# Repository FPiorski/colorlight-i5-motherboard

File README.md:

# colorlight-i5-motherboard
A base board for the colorlight i5 FPGA module with a bunch of connectors

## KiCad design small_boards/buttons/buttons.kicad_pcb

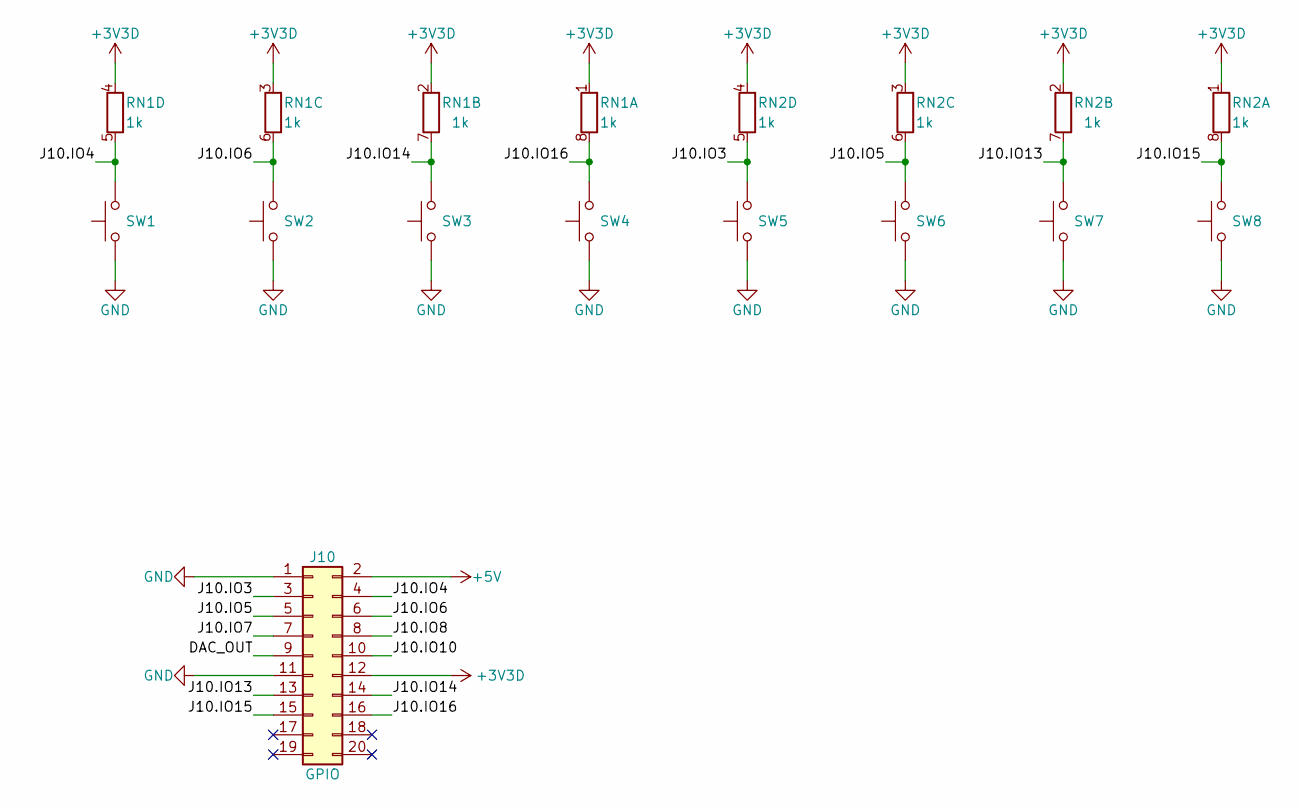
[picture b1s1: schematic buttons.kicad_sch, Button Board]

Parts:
J10: GPIO; PinSocket_2x10_P2.54mm_Vertical; LCSC C2897411
RN1, RN2: 1k; R_Array_Convex_4x0603; LCSC C160614
SW1, SW2, SW3, SW4, SW5, SW6, SW7, SW8: SW_Push_1P1T_NO_6x6mm_H9.5mm; LCSC C294566

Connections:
+3V3D: J10.12, RN1.1 (R1.1), RN1.2 (R2.1), RN1.3 (R3.1), RN1.4 (R4.1), RN2.1 (R1.1), RN2.2 (R2.1), RN2.3 (R3.1), RN2.4 (R4.1)
+5V: J10.2
/DAC_OUT: J10.9
/J10.IO3: J10.3, RN2.5 (R4.2), SW5.2
/J10.IO4: J10.4, RN1.5 (R4.2), SW1.2
/J10.IO5: J10.5, RN2.6 (R3.2), SW6.2
/J10.IO6: J10.6, RN1.6 (R3.2), SW2.2
/J10.IO7: J10.7
/J10.IO8: J10.8
/J10.IO10: J10.10
/J10.IO13: J10.13, RN2.7 (R2.2), SW7.2
/J10.IO14: J10.14, RN1.7 (R2.2), SW3.2
/J10.IO15: J10.15, RN2.8 (R1.2), SW8.2
/J10.IO16: J10.16, RN1.8 (R1.2), SW4.2
GND: J10.1, J10.11, SW1.1, SW2.1, SW3.1, SW4.1, SW5.1, SW6.1, SW7.1, SW8.1

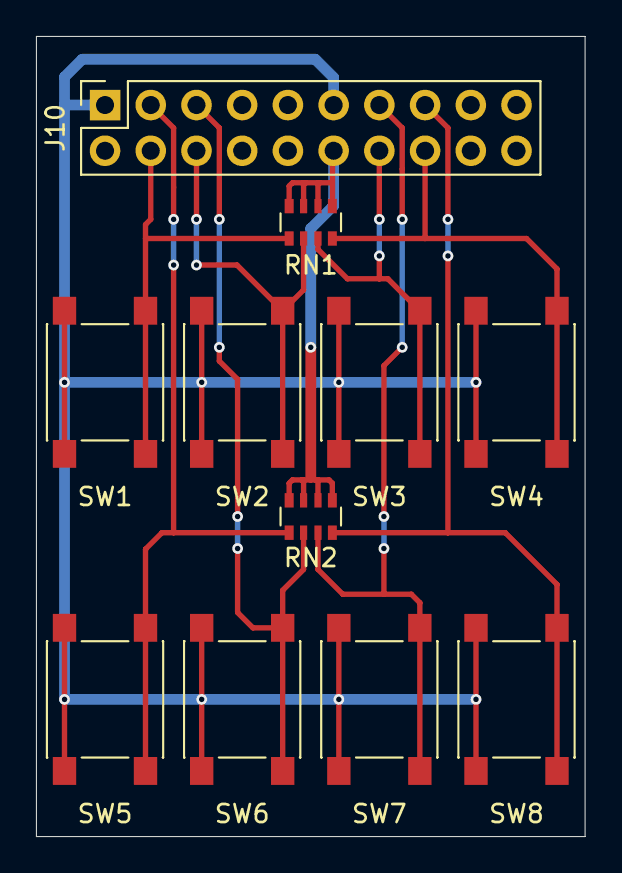
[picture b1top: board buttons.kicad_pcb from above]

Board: 2 copper layers, 30.5 x 44.5 mm, 11 parts (0 on the bottom side), 10 nets.

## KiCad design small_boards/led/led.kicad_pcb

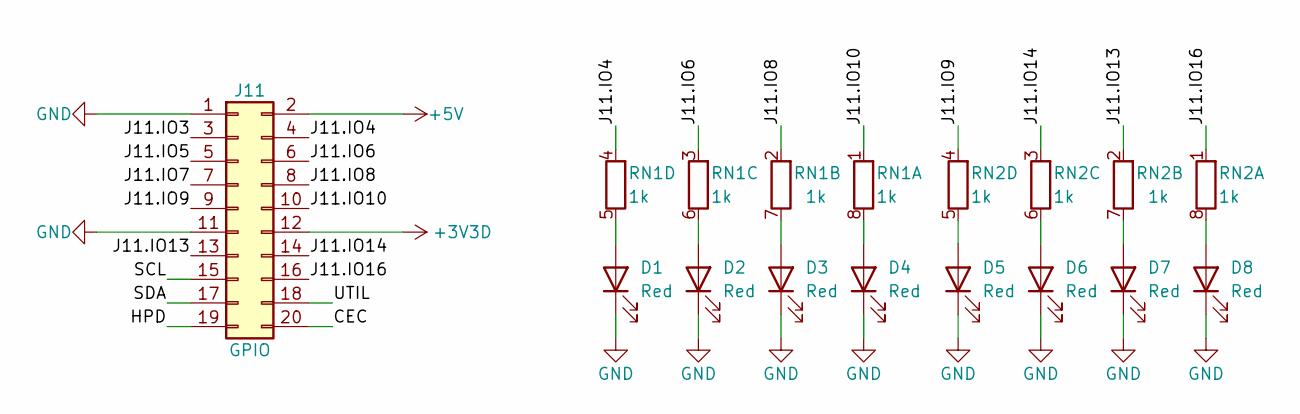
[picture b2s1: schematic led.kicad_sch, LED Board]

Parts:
D1, D2, D3, D4, D5, D6, D7, D8: Red; LED_0805_2012Metric_Pad1.15x1.40mm_HandSolder; LCSC C84256
J11: GPIO; PinSocket_2x10_P2.54mm_Vertical; LCSC C2897411
RN1, RN2: 1k; R_Array_Convex_4x0603; LCSC C160614

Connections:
+3V3D: J11.12
+5V: J11.2
/CEC: J11.20
/HPD: J11.19
/J11.IO3: J11.3
/J11.IO4: J11.4, RN1.4 (R4.1)
/J11.IO5: J11.5
/J11.IO6: J11.6, RN1.3 (R3.1)
/J11.IO7: J11.7
/J11.IO8: J11.8, RN1.2 (R2.1)
/J11.IO9: J11.9, RN2.4 (R4.1)
/J11.IO10: J11.10, RN1.1 (R1.1)
/J11.IO13: J11.13, RN2.2 (R2.1)
/J11.IO14: J11.14, RN2.3 (R3.1)
/J11.IO16: J11.16, RN2.1 (R1.1)
/SCL: J11.15
/SDA: J11.17
/UTIL: J11.18
GND: D1.1 (K), D2.1 (K), D3.1 (K), D4.1 (K), D5.1 (K), D6.1 (K), D7.1 (K), D8.1 (K), J11.1, J11.11
unnamed: D1.2 (A), RN1.5 (R4.2)
unnamed: D2.2 (A), RN1.6 (R3.2)
unnamed: D3.2 (A), RN1.7 (R2.2)
unnamed: D4.2 (A), RN1.8 (R1.2)
unnamed: D5.2 (A), RN2.5 (R4.2)
unnamed: D6.2 (A), RN2.6 (R3.2)
unnamed: D7.2 (A), RN2.7 (R2.2)
unnamed: D8.2 (A), RN2.8 (R1.2)

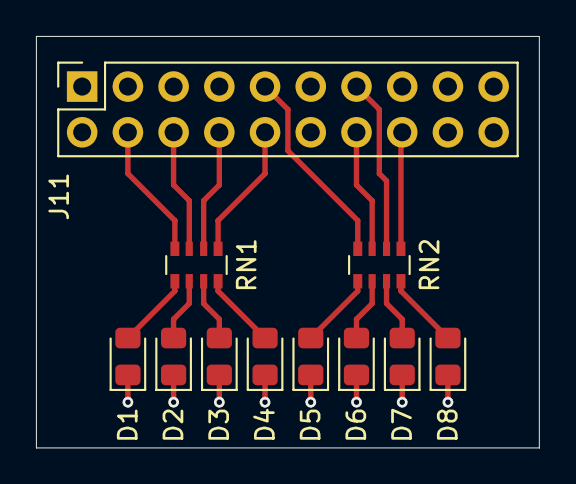
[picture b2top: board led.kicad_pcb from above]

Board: 2 copper layers, 27.9 x 22.9 mm, 11 parts (0 on the bottom side), 17 nets.

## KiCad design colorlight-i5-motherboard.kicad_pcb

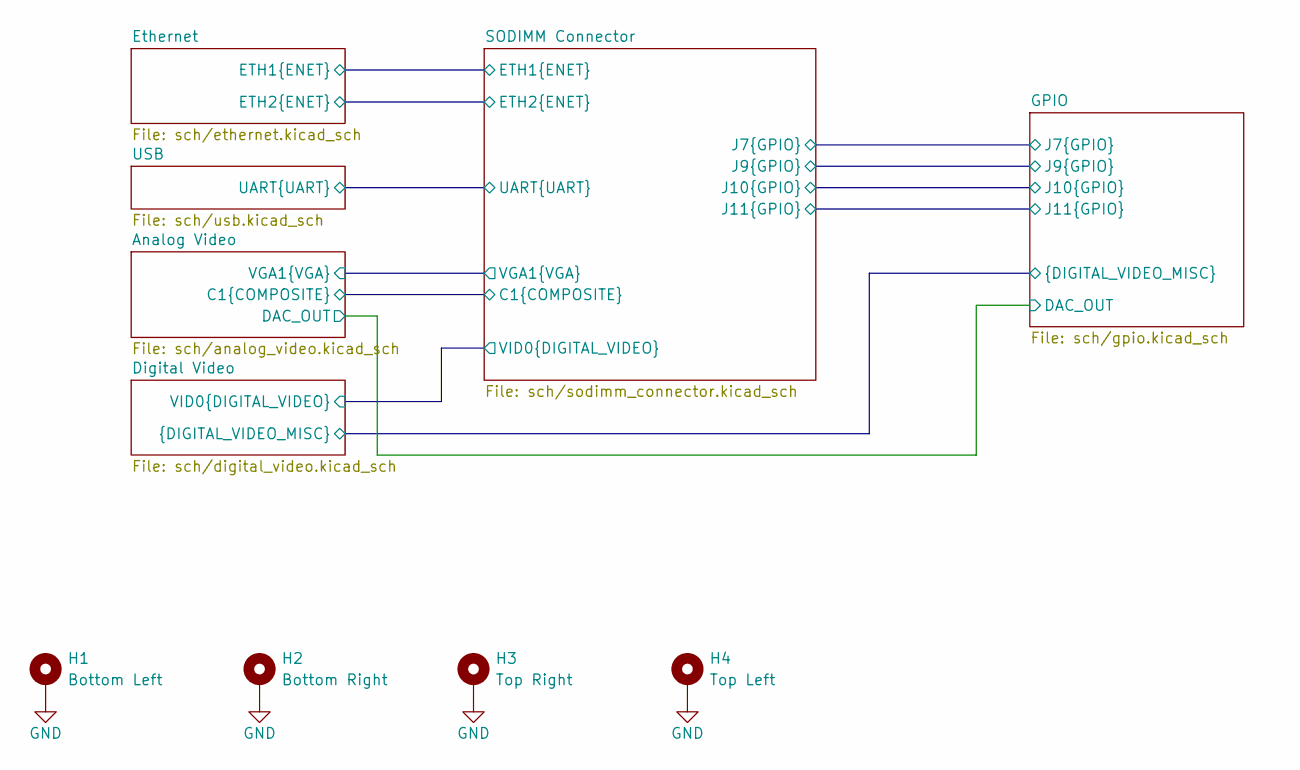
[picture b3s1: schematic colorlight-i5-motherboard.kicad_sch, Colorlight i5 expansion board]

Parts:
H1, H2, H3, H4: MountingHole_3.2mm_M3_Pad_Via

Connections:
GND: H1.1, H2.1, H3.1, H4.1; also elsewhere on the board

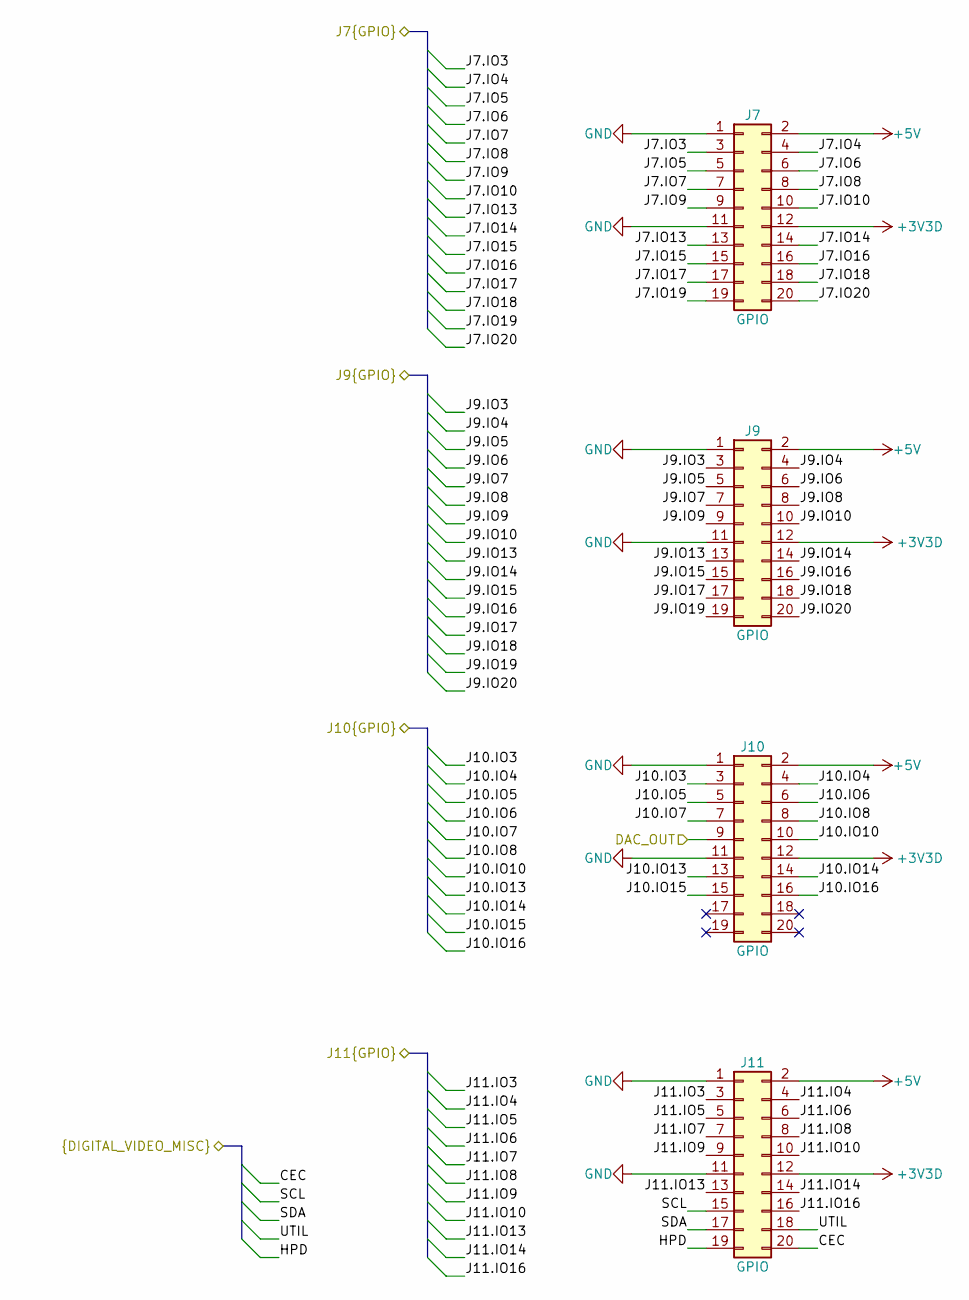
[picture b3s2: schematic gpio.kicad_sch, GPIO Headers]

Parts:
J7, J9, J10, J11: GPIO; PinHeader_2x10_P2.54mm_Vertical; LCSC C492427

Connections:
+3V3D: J7.12, J9.12, J10.12, J11.12; also elsewhere on the board
+5V: J7.2, J9.2, J10.2, J11.2; also elsewhere on the board
/Analog Video/DAC_OUT: J10.9; also elsewhere on the board
/Digital Video/CEC: J11.20; also elsewhere on the board
/Digital Video/HPD: J11.19; also elsewhere on the board
/Digital Video/SCL: J11.15; also elsewhere on the board
/Digital Video/SDA: J11.17; also elsewhere on the board
/Digital Video/UTIL: J11.18; also elsewhere on the board
/GPIO/J7.IO3: J7.3; also elsewhere on the board
/GPIO/J7.IO4: J7.4; also elsewhere on the board
/GPIO/J7.IO5: J7.5; also elsewhere on the board
/GPIO/J7.IO6: J7.6; also elsewhere on the board
/GPIO/J7.IO7: J7.7; also elsewhere on the board
/GPIO/J7.IO8: J7.8; also elsewhere on the board
/GPIO/J7.IO9: J7.9; also elsewhere on the board
/GPIO/J7.IO10: J7.10; also elsewhere on the board
/GPIO/J7.IO13: J7.13; also elsewhere on the board
/GPIO/J7.IO14: J7.14; also elsewhere on the board
/GPIO/J7.IO15: J7.15; also elsewhere on the board
/GPIO/J7.IO16: J7.16; also elsewhere on the board
/GPIO/J7.IO17: J7.17; also elsewhere on the board
/GPIO/J7.IO18: J7.18; also elsewhere on the board
/GPIO/J7.IO19: J7.19; also elsewhere on the board
/GPIO/J7.IO20: J7.20; also elsewhere on the board
/GPIO/J9.IO3: J9.3; also elsewhere on the board
/GPIO/J9.IO4: J9.4; also elsewhere on the board
/GPIO/J9.IO5: J9.5; also elsewhere on the board
/GPIO/J9.IO6: J9.6; also elsewhere on the board
/GPIO/J9.IO7: J9.7; also elsewhere on the board
/GPIO/J9.IO8: J9.8; also elsewhere on the board
/GPIO/J9.IO9: J9.9; also elsewhere on the board
/GPIO/J9.IO10: J9.10; also elsewhere on the board
/GPIO/J9.IO13: J9.13; also elsewhere on the board
/GPIO/J9.IO14: J9.14; also elsewhere on the board
/GPIO/J9.IO15: J9.15; also elsewhere on the board
/GPIO/J9.IO16: J9.16; also elsewhere on the board
/GPIO/J9.IO17: J9.17; also elsewhere on the board
/GPIO/J9.IO18: J9.18; also elsewhere on the board
/GPIO/J9.IO19: J9.19; also elsewhere on the board
/GPIO/J9.IO20: J9.20; also elsewhere on the board
/GPIO/J10.IO3: J10.3; also elsewhere on the board
/GPIO/J10.IO4: J10.4; also elsewhere on the board
/GPIO/J10.IO5: J10.5; also elsewhere on the board
/GPIO/J10.IO6: J10.6; also elsewhere on the board
/GPIO/J10.IO7: J10.7; also elsewhere on the board
/GPIO/J10.IO8: J10.8; also elsewhere on the board
/GPIO/J10.IO10: J10.10; also elsewhere on the board
/GPIO/J10.IO13: J10.13; also elsewhere on the board
/GPIO/J10.IO14: J10.14; also elsewhere on the board
/GPIO/J10.IO15: J10.15; also elsewhere on the board
/GPIO/J10.IO16: J10.16; also elsewhere on the board
/GPIO/J11.IO3: J11.3; also elsewhere on the board
/GPIO/J11.IO4: J11.4; also elsewhere on the board
/GPIO/J11.IO5: J11.5; also elsewhere on the board
/GPIO/J11.IO6: J11.6; also elsewhere on the board
/GPIO/J11.IO7: J11.7; also elsewhere on the board
/GPIO/J11.IO8: J11.8; also elsewhere on the board
/GPIO/J11.IO9: J11.9; also elsewhere on the board
/GPIO/J11.IO10: J11.10; also elsewhere on the board
/GPIO/J11.IO13: J11.13; also elsewhere on the board
/GPIO/J11.IO14: J11.14; also elsewhere on the board
/GPIO/J11.IO16: J11.16; also elsewhere on the board
GND: J7.1, J7.11, J9.1, J9.11, J10.1, J10.11, J11.1, J11.11; also elsewhere on the board

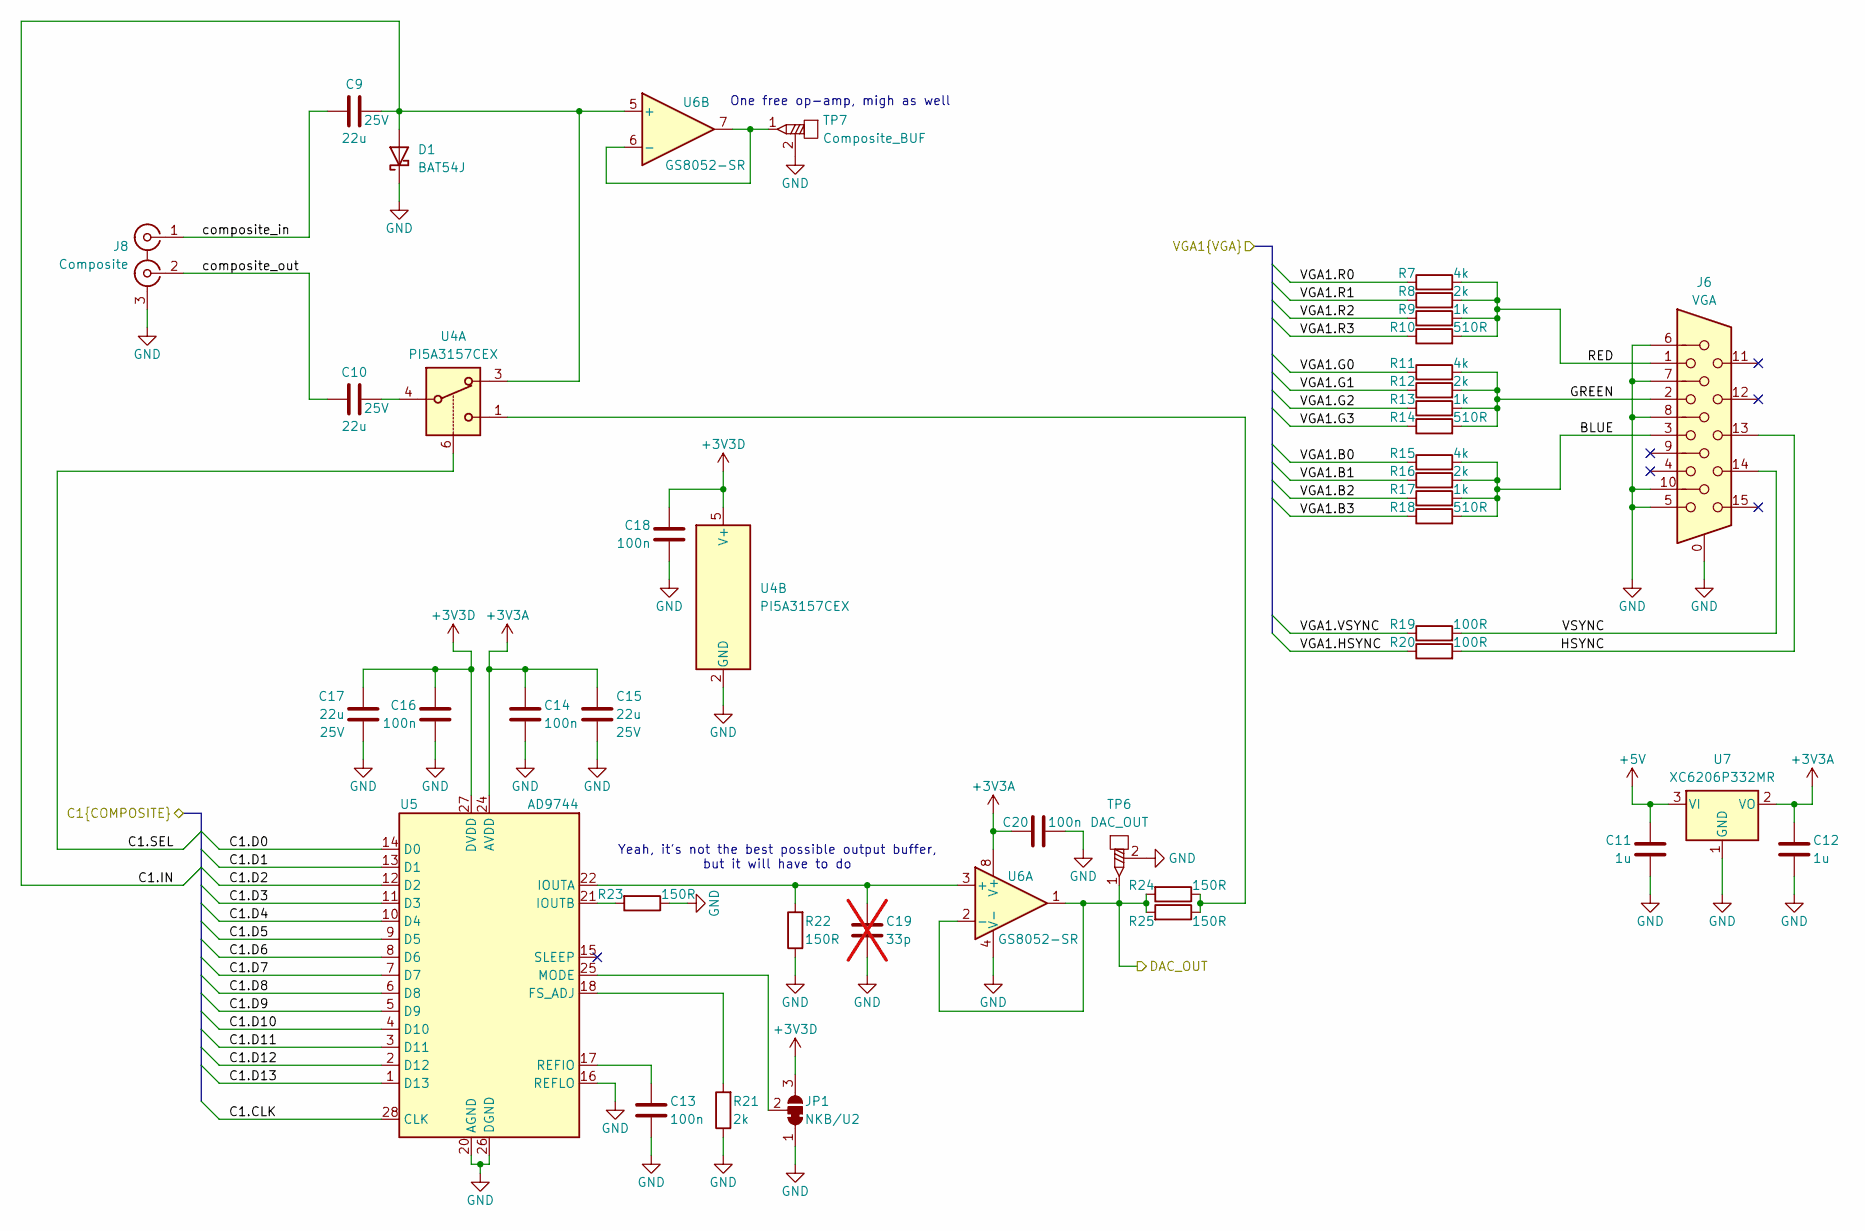
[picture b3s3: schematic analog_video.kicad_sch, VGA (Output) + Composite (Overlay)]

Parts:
C9, C10, C15, C17: 22u; C_0805_2012Metric; Voltage 25V
C11, C12: 1u; C_0402_1005Metric
C13, C14, C16, C18, C20: 100n; C_0402_1005Metric
C19: 33p; C_0402_1005Metric; not fitted
D1: BAT54J; D_SOD-323F; LCSC C130415
J6: VGA; DSUB-15-HD_Female_Horizontal_P2.29x1.98mm_EdgePinOffset8.35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; LCSC C138387
J8: Composite; XDJK-0271-1650; LCSC C7527522
JP1: SolderJumper_3_Bridged12; SolderJumper-3_P1.3mm_Bridged12_Pad1.0x1.5mm
R7, R11, R15: 4k; R_0402_1005Metric
R8, R12, R16, R21: 2k; R_0402_1005Metric
R9, R13, R17: 1k; R_0402_1005Metric
R10, R14, R18: 510R; R_0402_1005Metric
R19, R20: 100R; R_0402_1005Metric
R22, R23, R24, R25: 150R; R_0402_1005Metric
TP6, TP7: TestPoint_Probe; TestPoint_Oscilloscope_Probe
U4: PI5A3157CEX; SOT-363_SC-70-6; LCSC C2673088
U5: AD9744; TSSOP-28_4.4x9.7mm_P0.65mm; LCSC C461519
U6: GS8052-SR; SOIC-8_3.9x4.9mm_P1.27mm; LCSC C157722
U7: XC6206P332MR; SOT-23-3; LCSC C5148692

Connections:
+3V3A: C12.1, C14.1, C15.2, C20.1, U5.24 (AVDD), U6.8 (V+), U7.2 (VO)
+3V3D: C16.1, C17.2, C18.1, JP1.3 (B), U4.5 (V+), U5.27 (DVDD); also elsewhere on the board
+5V: C11.1, U7.3 (VI); also elsewhere on the board
/Analog Video/BLUE: J6.3, R15.2, R16.2, R17.2, R18.2
/Analog Video/C1.CLK: U5.28 (CLK); also elsewhere on the board
/Analog Video/C1.D0: U5.14 (D0); also elsewhere on the board
/Analog Video/C1.D1: U5.13 (D1); also elsewhere on the board
/Analog Video/C1.D2: U5.12 (D2); also elsewhere on the board
/Analog Video/C1.D3: U5.11 (D3); also elsewhere on the board
/Analog Video/C1.D4: U5.10 (D4); also elsewhere on the board
/Analog Video/C1.D5: U5.9 (D5); also elsewhere on the board
/Analog Video/C1.D6: U5.8 (D6); also elsewhere on the board
/Analog Video/C1.D7: U5.7 (D7); also elsewhere on the board
/Analog Video/C1.D8: U5.6 (D8); also elsewhere on the board
/Analog Video/C1.D9: U5.5 (D9); also elsewhere on the board
/Analog Video/C1.D10: U5.4 (D10); also elsewhere on the board
/Analog Video/C1.D11: U5.3 (D11); also elsewhere on the board
/Analog Video/C1.D12: U5.2 (D12); also elsewhere on the board
/Analog Video/C1.D13: U5.1 (D13); also elsewhere on the board
/Analog Video/C1.IN: C9.2, D1.2 (A), U4.3, U6.5 (+); also elsewhere on the board
/Analog Video/C1.SEL: U4.6; also elsewhere on the board
/Analog Video/DAC_OUT: R24.2, R25.2, TP6.1, U6.1, U6.2 (-); also elsewhere on the board
/Analog Video/GREEN: J6.2, R11.2, R12.2, R13.2, R14.2
/Analog Video/HSYNC: J6.13, R20.2
/Analog Video/RED: J6.1, R7.2, R8.2, R9.2, R10.2
/Analog Video/VGA1.B0: R15.1; also elsewhere on the board
/Analog Video/VGA1.B1: R16.1; also elsewhere on the board
/Analog Video/VGA1.B2: R17.1; also elsewhere on the board
/Analog Video/VGA1.B3: R18.1; also elsewhere on the board
/Analog Video/VGA1.G0: R11.1; also elsewhere on the board
/Analog Video/VGA1.G1: R12.1; also elsewhere on the board
/Analog Video/VGA1.G2: R13.1; also elsewhere on the board
/Analog Video/VGA1.G3: R14.1; also elsewhere on the board
/Analog Video/VGA1.HSYNC: R20.1; also elsewhere on the board
/Analog Video/VGA1.R0: R7.1; also elsewhere on the board
/Analog Video/VGA1.R1: R8.1; also elsewhere on the board
/Analog Video/VGA1.R2: R9.1; also elsewhere on the board
/Analog Video/VGA1.R3: R10.1; also elsewhere on the board
/Analog Video/VGA1.VSYNC: R19.1; also elsewhere on the board
/Analog Video/VSYNC: J6.14, R19.2
/Analog Video/composite_in: C9.1, J8.1 (IN1)
/Analog Video/composite_out: C10.1, J8.2 (IN2)
GND: C11.2, C12.2, C13.2, C14.2, C15.1, C16.2, C17.1, C18.2, C19.2, C20.2, D1.1 (K), J6.0, J6.5, J6.6, J6.7, J6.8, J6.10, J8.3 (EXT), JP1.1 (A), R21.1, R22.1, R23.1, TP6.2, TP7.2, U4.2 (GND), U5.16 (REFLO), U5.20 (AGND), U5.26 (DGND), U6.4 (V-), U7.1 (GND); also elsewhere on the board
unnamed: C10.2, U4.4
unnamed: JP1.2 (C), U5.25 (MODE)
unnamed: R24.1, R25.1, U4.1
unnamed: R21.2, U5.18 (FS_ADJ)
unnamed: C19.1, R22.2, U5.22 (IOUTA), U6.3 (+)
unnamed: R23.2, U5.21 (IOUTB)
unnamed: C13.1, U5.17 (REFIO)
unnamed: TP7.1, U6.6 (-), U6.7

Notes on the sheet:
One free op-amp, migh as well
Yeah, it's not the best possible output buffer, but it will have to do

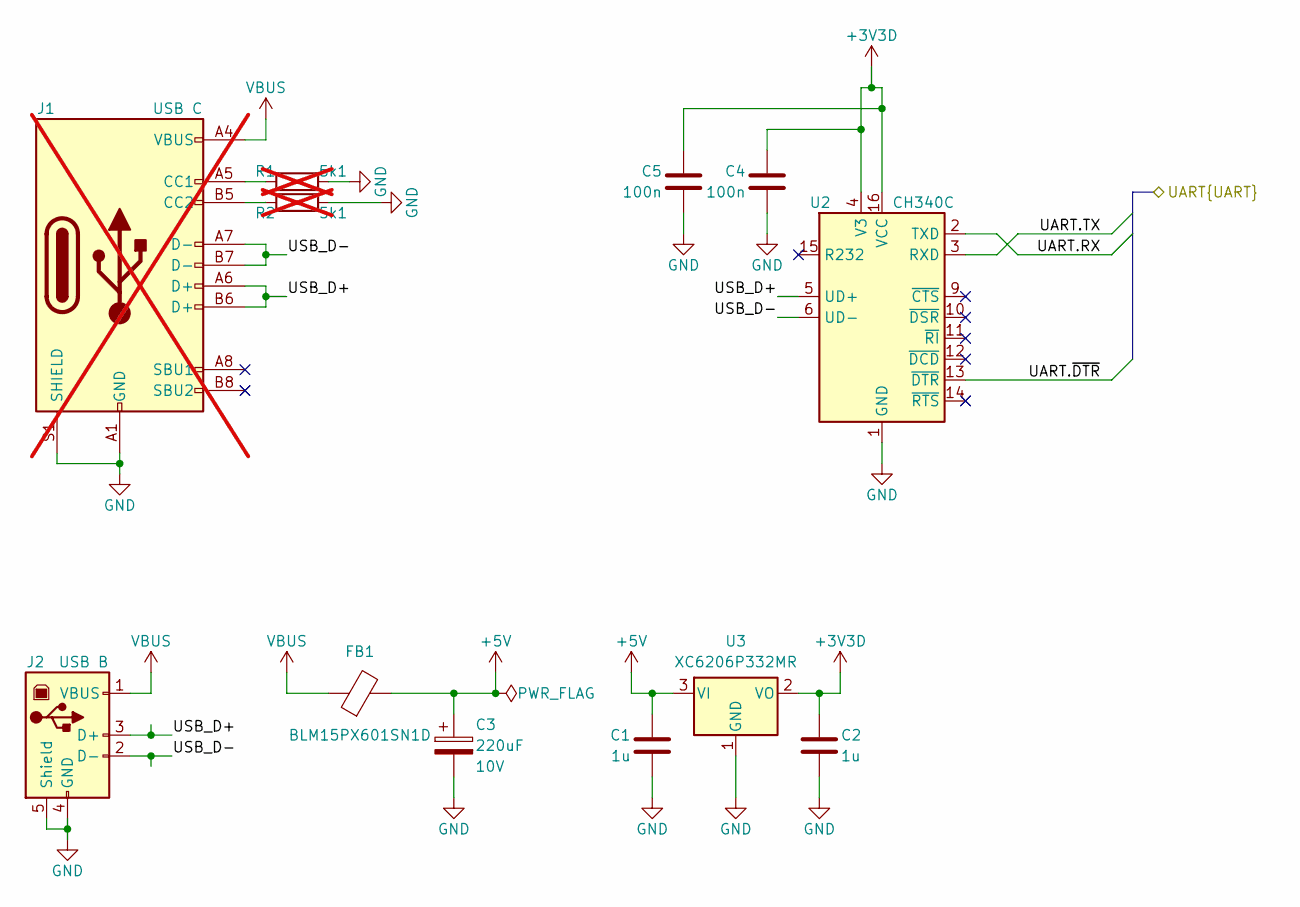
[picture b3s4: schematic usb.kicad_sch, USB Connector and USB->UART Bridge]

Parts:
C1, C2: 1u; C_0402_1005Metric
C3: 220uF; CP_Radial_D6.3mm_P2.50mm; Voltage 10V; LCSC C43318
C4, C5: 100n; C_0402_1005Metric
FB1: BLM15PX601SN1D; L_0402_1005Metric; LCSC C160977
J1: USB C; USB_C_Receptacle_HRO_TYPE-C-31-M-12; LCSC C165948; not fitted
J2: USB B; USB_B_OST_USB-B1HSxx_Horizontal; LCSC C46392
R1, R2: 5k1; R_0402_1005Metric; not fitted
U2: CH340C; SOIC-16_3.9x9.9mm_P1.27mm; LCSC C84681
U3: XC6206P332MR; SOT-23-3; LCSC C5148692

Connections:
+3V3D: C2.1, C4.1, C5.1, U2.4 (V3), U2.16 (VCC), U3.2 (VO); also elsewhere on the board
+5V: C1.1, C3.1, FB1.2, U3.3 (VI); also elsewhere on the board
/SODIMM Connector/UART.RX: U2.2 (TXD); also elsewhere on the board
/SODIMM Connector/UART.TX: U2.3 (RXD); also elsewhere on the board
/SODIMM Connector/UART.~DTR: U2.13 (~DTR); also elsewhere on the board
/USB/USB_D+: J1.A6 (D+), J1.B6 (D+), J2.3 (D+), U2.5 (UD+)
/USB/USB_D-: J1.A7 (D-), J1.B7 (D-), J2.2 (D-), U2.6 (UD-)
GND: C1.2, C2.2, C3.2, C4.2, C5.2, J1.A1 (GND), J1.A12 (GND), J1.B1 (GND), J1.B12 (GND), J1.S1 (SHIELD), J2.4 (GND), J2.5 (Shield), R1.2, R2.2, U2.1 (GND), U3.1 (GND); also elsewhere on the board
unnamed: J1.A5 (CC1), R1.1
unnamed: J1.B5 (CC2), R2.1
VBUS: FB1.1, J1.A4 (VBUS), J1.A9 (VBUS), J1.B4 (VBUS), J1.B9 (VBUS), J2.1 (VBUS)

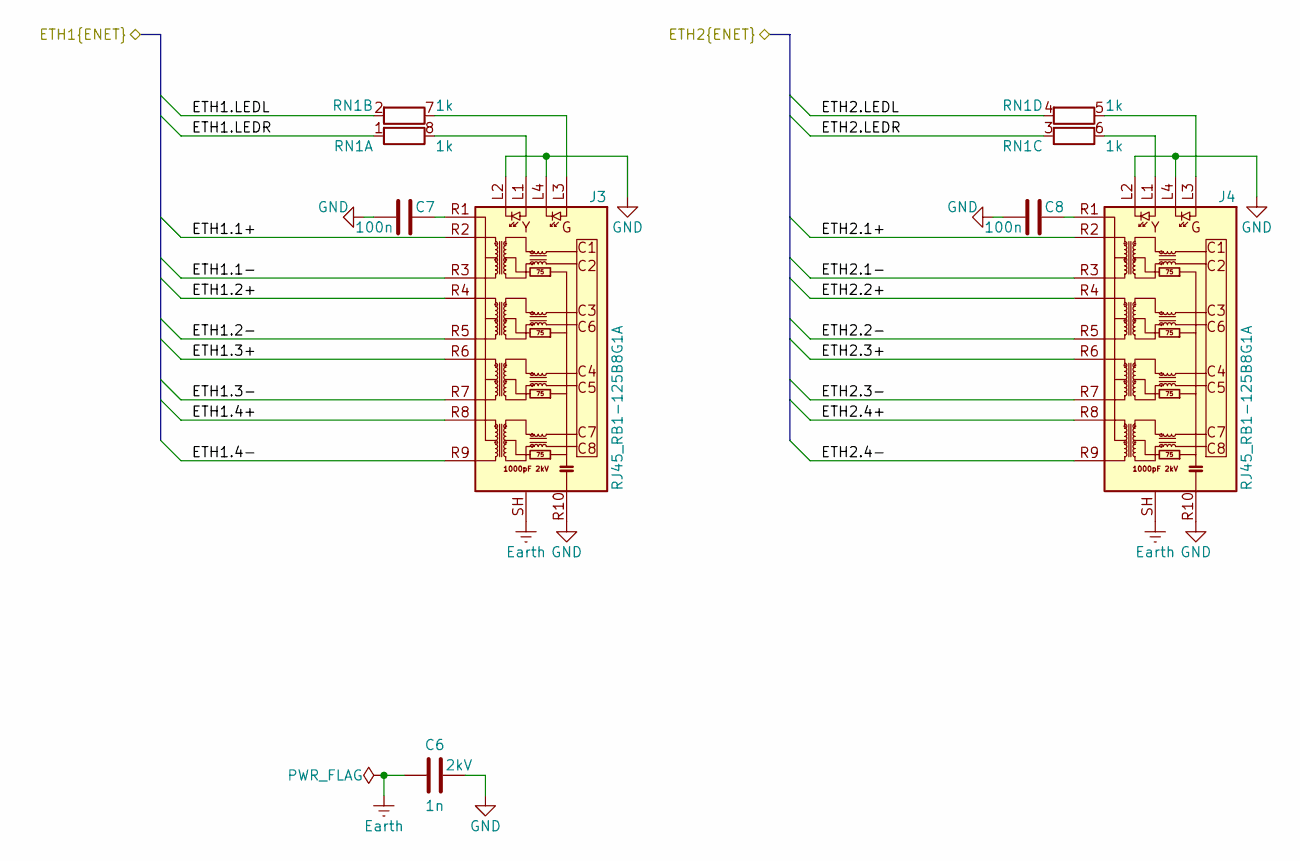
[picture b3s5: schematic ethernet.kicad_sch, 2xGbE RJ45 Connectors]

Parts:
C6: 1n; C_1206_3216Metric; Voltage 2kV; MPN 1206B102K202NT; LCSC C9196
C7, C8: 100n; C_0402_1005Metric
J3, J4: RJ45_RB1-125B8G1A; RJ45_UDE_RB1-125B8G1A; LCSC C363353
RN1: 1k; R_Array_Convex_4x0603; LCSC C160614

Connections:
/Ethernet/ETH1.1+: J3.R2 (TD1+); also elsewhere on the board
/Ethernet/ETH1.1-: J3.R3 (TD1-); also elsewhere on the board
/Ethernet/ETH1.2+: J3.R4 (TD2+); also elsewhere on the board
/Ethernet/ETH1.2-: J3.R5 (TD2-); also elsewhere on the board
/Ethernet/ETH1.3+: J3.R6 (TD3+); also elsewhere on the board
/Ethernet/ETH1.3-: J3.R7 (TD3-); also elsewhere on the board
/Ethernet/ETH1.4+: J3.R8 (TD4+); also elsewhere on the board
/Ethernet/ETH1.4-: J3.R9 (TD4-); also elsewhere on the board
/Ethernet/ETH1.LEDL: RN1.2 (R2.1); also elsewhere on the board
/Ethernet/ETH1.LEDR: RN1.1 (R1.1); also elsewhere on the board
/Ethernet/ETH2.1+: J4.R2 (TD1+); also elsewhere on the board
/Ethernet/ETH2.1-: J4.R3 (TD1-); also elsewhere on the board
/Ethernet/ETH2.2+: J4.R4 (TD2+); also elsewhere on the board
/Ethernet/ETH2.2-: J4.R5 (TD2-); also elsewhere on the board
/Ethernet/ETH2.3+: J4.R6 (TD3+); also elsewhere on the board
/Ethernet/ETH2.3-: J4.R7 (TD3-); also elsewhere on the board
/Ethernet/ETH2.4+: J4.R8 (TD4+); also elsewhere on the board
/Ethernet/ETH2.4-: J4.R9 (TD4-); also elsewhere on the board
/Ethernet/ETH2.LEDL: RN1.4 (R4.1); also elsewhere on the board
/Ethernet/ETH2.LEDR: RN1.3 (R3.1); also elsewhere on the board
Earth: C6.1, J3.SH, J4.SH
GND: C6.2, C7.2, C8.2, J3.L2, J3.L4, J3.R10 (GND), J4.L2, J4.L4, J4.R10 (GND); also elsewhere on the board
unnamed: C7.1, J3.R1 (CT)
unnamed: C8.1, J4.R1 (CT)
unnamed: J3.L1, RN1.8 (R1.2)
unnamed: J3.L3, RN1.7 (R2.2)
unnamed: J4.L1, RN1.6 (R3.2)
unnamed: J4.L3, RN1.5 (R4.2)

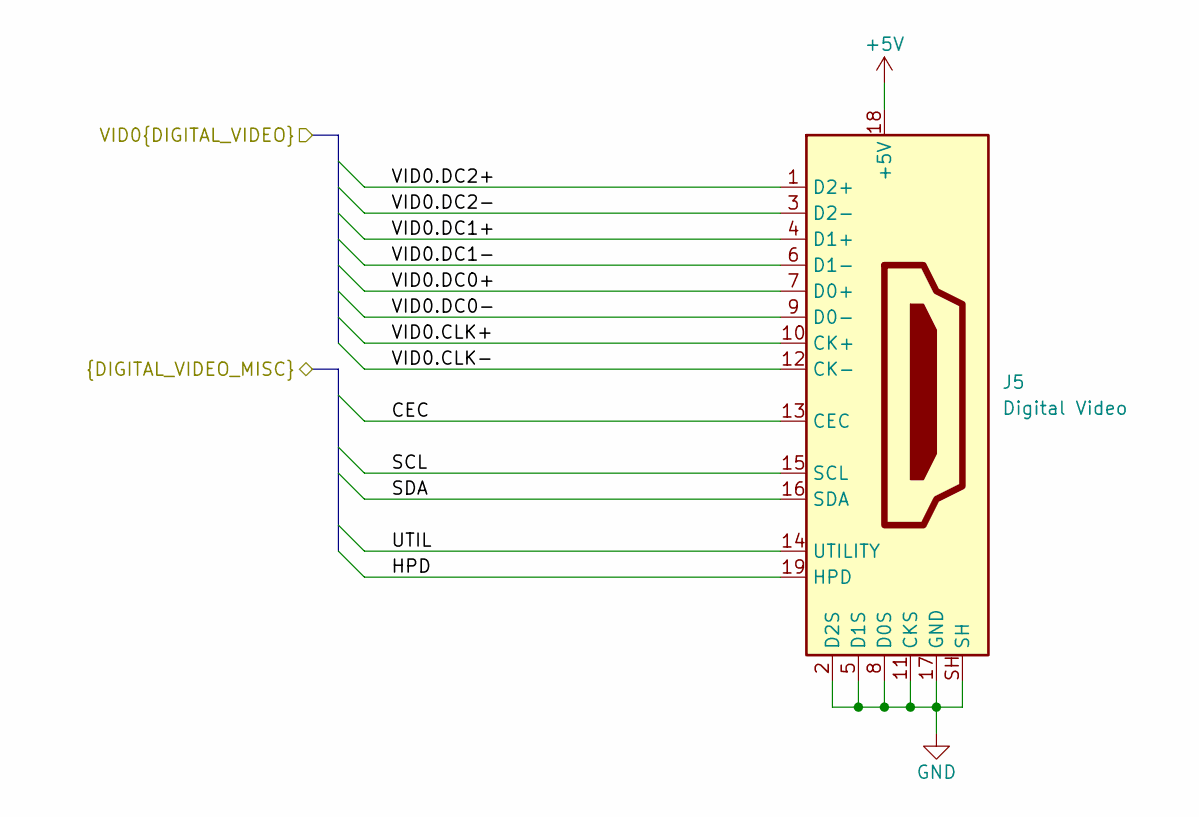
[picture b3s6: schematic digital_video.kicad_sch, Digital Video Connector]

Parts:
J5: Digital Video; HDMI_A_Molex_208658-1001_Horizontal; LCSC C341098

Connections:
+5V: J5.18 (+5V); also elsewhere on the board
/Digital Video/CEC: J5.13 (CEC); also elsewhere on the board
/Digital Video/HPD: J5.19 (HPD); also elsewhere on the board
/Digital Video/SCL: J5.15 (SCL); also elsewhere on the board
/Digital Video/SDA: J5.16 (SDA); also elsewhere on the board
/Digital Video/UTIL: J5.14 (UTILITY); also elsewhere on the board
/Digital Video/VID0.CLK+: J5.10 (CK+); also elsewhere on the board
/Digital Video/VID0.CLK-: J5.12 (CK-); also elsewhere on the board
/Digital Video/VID0.DC0+: J5.7 (D0+); also elsewhere on the board
/Digital Video/VID0.DC0-: J5.9 (D0-); also elsewhere on the board
/Digital Video/VID0.DC1+: J5.4 (D1+); also elsewhere on the board
/Digital Video/VID0.DC1-: J5.6 (D1-); also elsewhere on the board
/Digital Video/VID0.DC2+: J5.1 (D2+); also elsewhere on the board
/Digital Video/VID0.DC2-: J5.3 (D2-); also elsewhere on the board
GND: J5.2 (D2S), J5.5 (D1S), J5.8 (D0S), J5.11 (CKS), J5.17 (GND), J5.SH; also elsewhere on the board

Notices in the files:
colorlight-i5-motherboard.kicad_sch:
CERN-OHL-W-2.0
